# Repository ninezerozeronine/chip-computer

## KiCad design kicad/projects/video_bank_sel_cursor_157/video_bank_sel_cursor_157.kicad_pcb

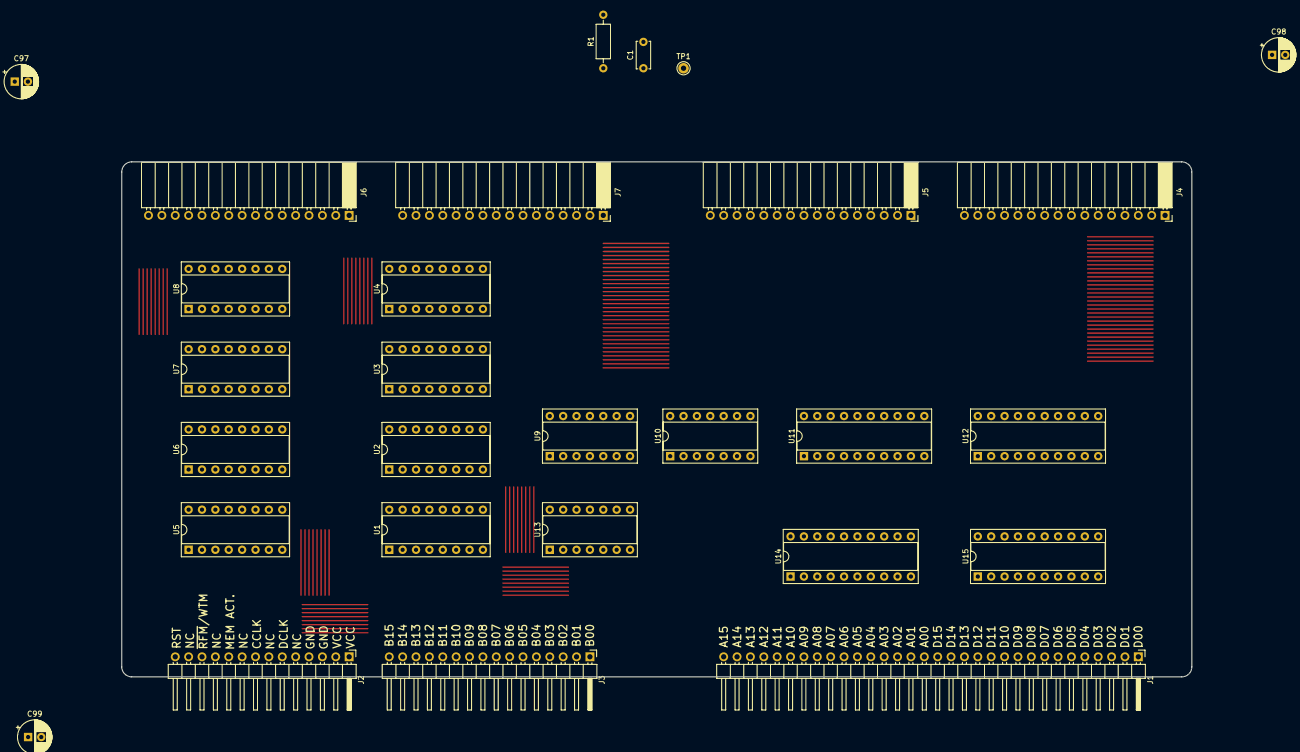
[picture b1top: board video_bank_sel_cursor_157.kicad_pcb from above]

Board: 2 copper layers, 203.2 x 97.8 mm, 28 parts (0 on the bottom side), 2 nets.

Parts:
C1: C; C_Disc_D5.0mm_W2.5mm_P5.00mm
C97, C98, C99: C_Polarized; CP_Radial_D6.3mm_P2.50mm
J1: peripheral_addr_bus_connector; peripheral-backplane-data-addr-anno
J2: peripheral_aux_connector; peripheral-backplane-aux
J3: peripheral_membank_connector; peripheral-backplane-membank
J4, J5, J6, J7: Conn_01x16_Socket; PinSocket_1x16_P2.54mm_Horizontal
R1: R_US; R_Axial_DIN0207_L6.3mm_D2.5mm_P10.16mm_Horizontal
TP1: TestPoint; Pin_D1.0mm_L10.0mm
U1, U2, U3, U4, U5, U6, U7, U8: 74HC157; DIP-16_W7.62mm_Socket
U9, U10: 74HC10; DIP-14_W7.62mm_Socket
U11, U12: 74HC377; DIP-20_W7.62mm_Socket
U13: 74HC04; DIP-14_W7.62mm_Socket
U14, U15: 74HC245; DIP-20_W7.62mm_Socket

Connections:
GND: C97.2, C98.2, C99.2, J2.3 (GND), J2.4 (GND)
VCC: C97.1, C98.1, C99.1, J2.1 (VCC), J2.2 (VCC)

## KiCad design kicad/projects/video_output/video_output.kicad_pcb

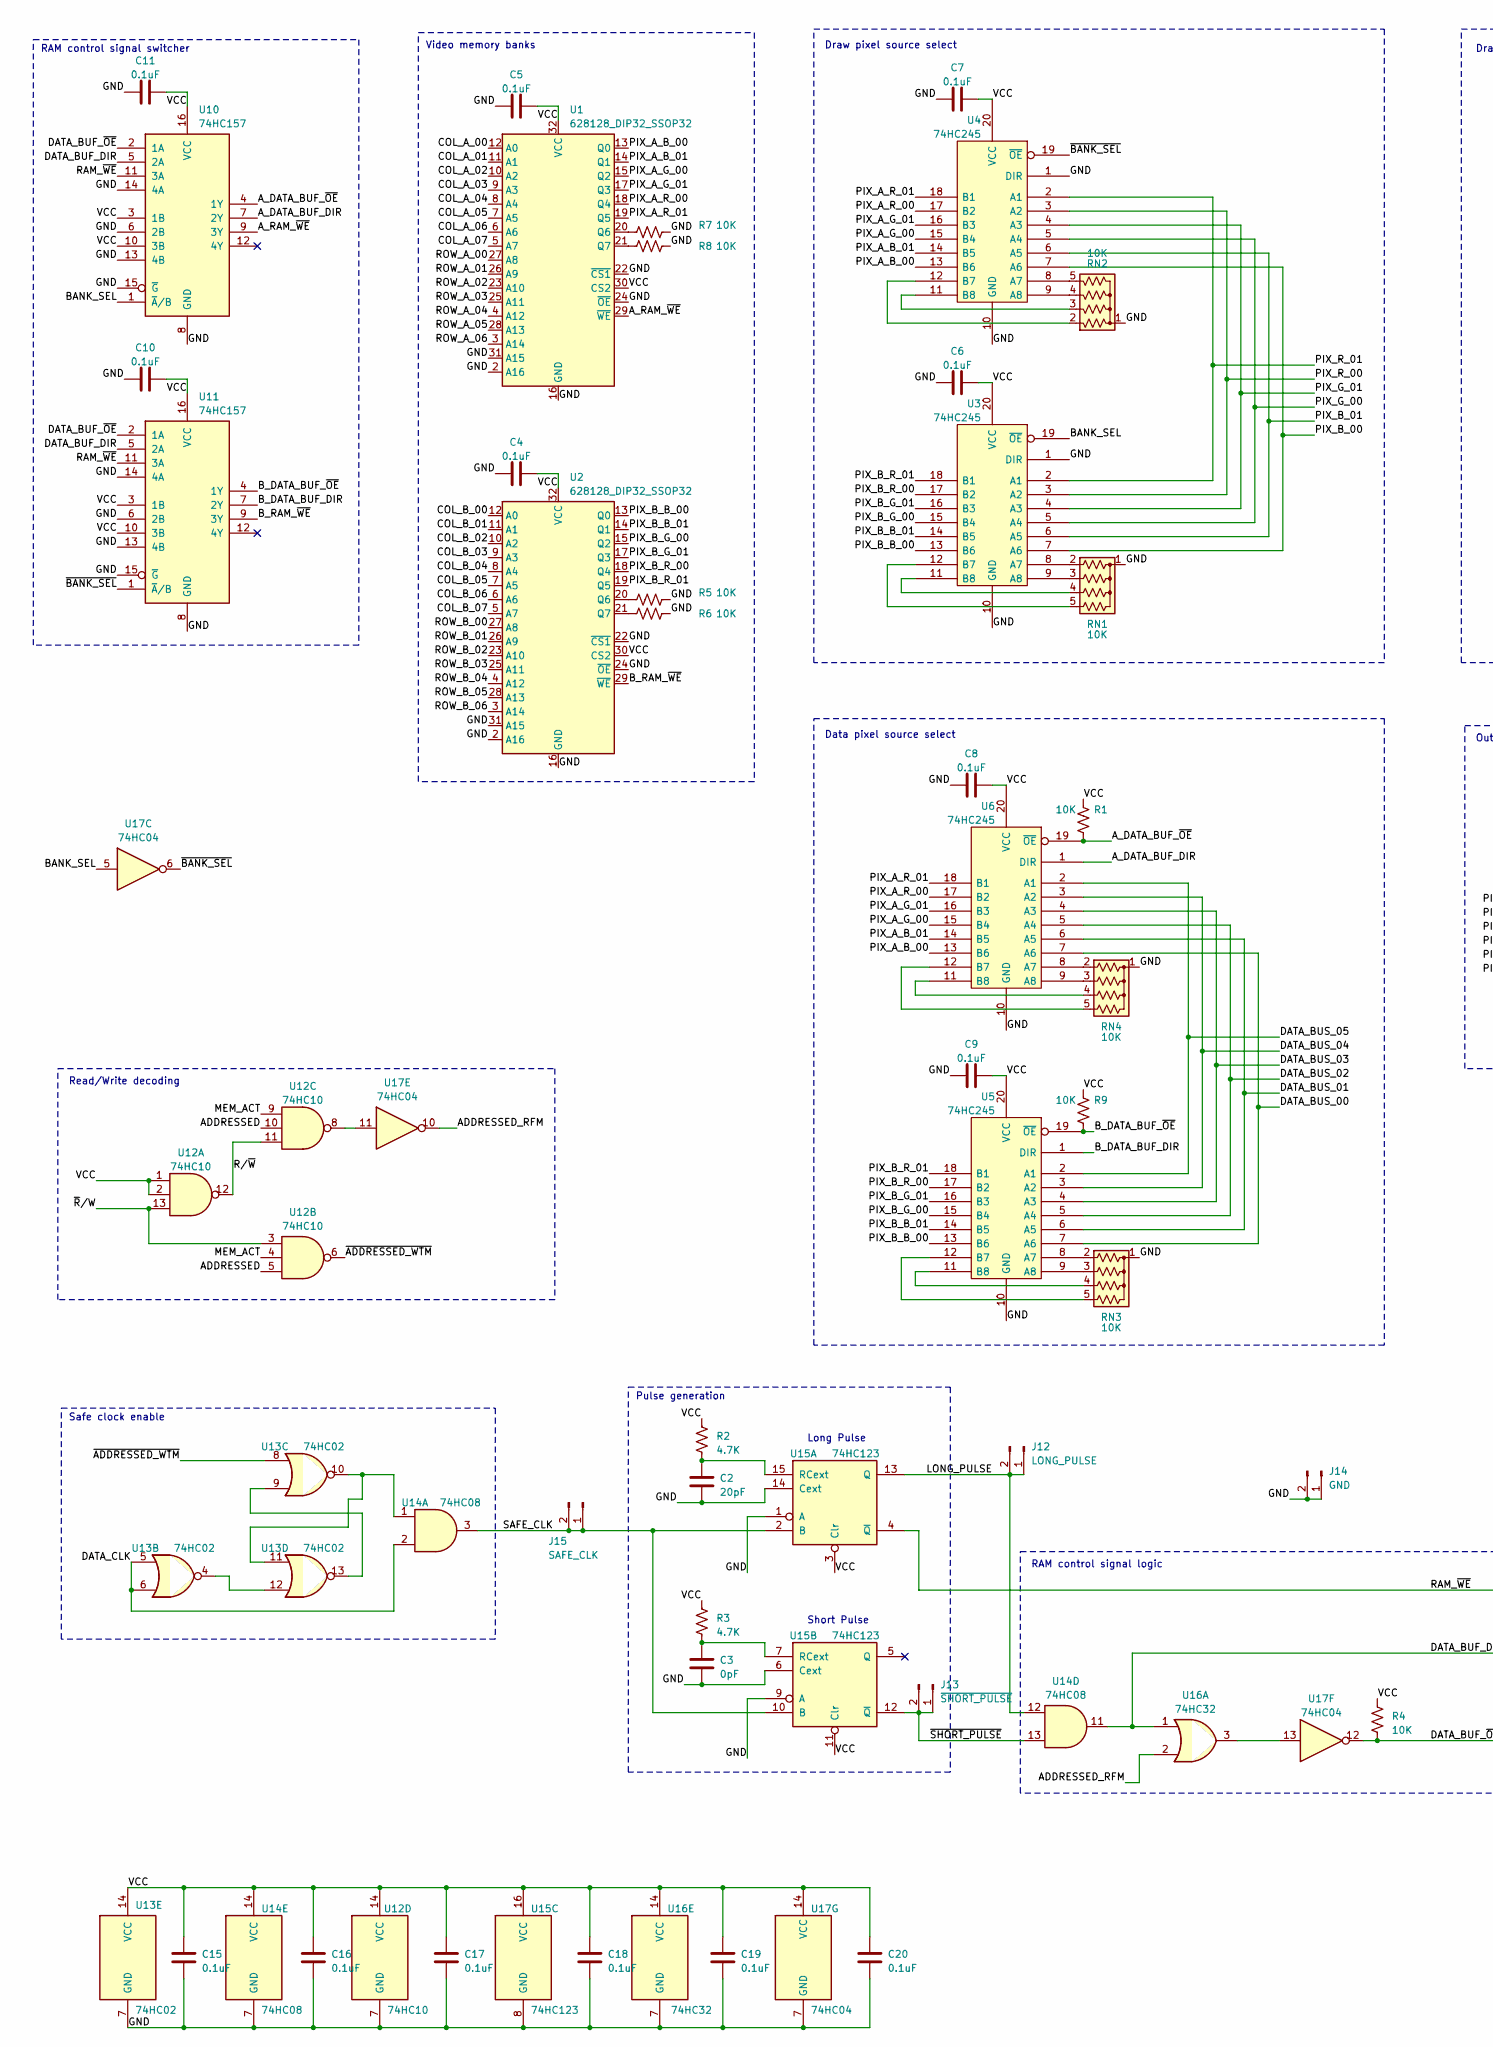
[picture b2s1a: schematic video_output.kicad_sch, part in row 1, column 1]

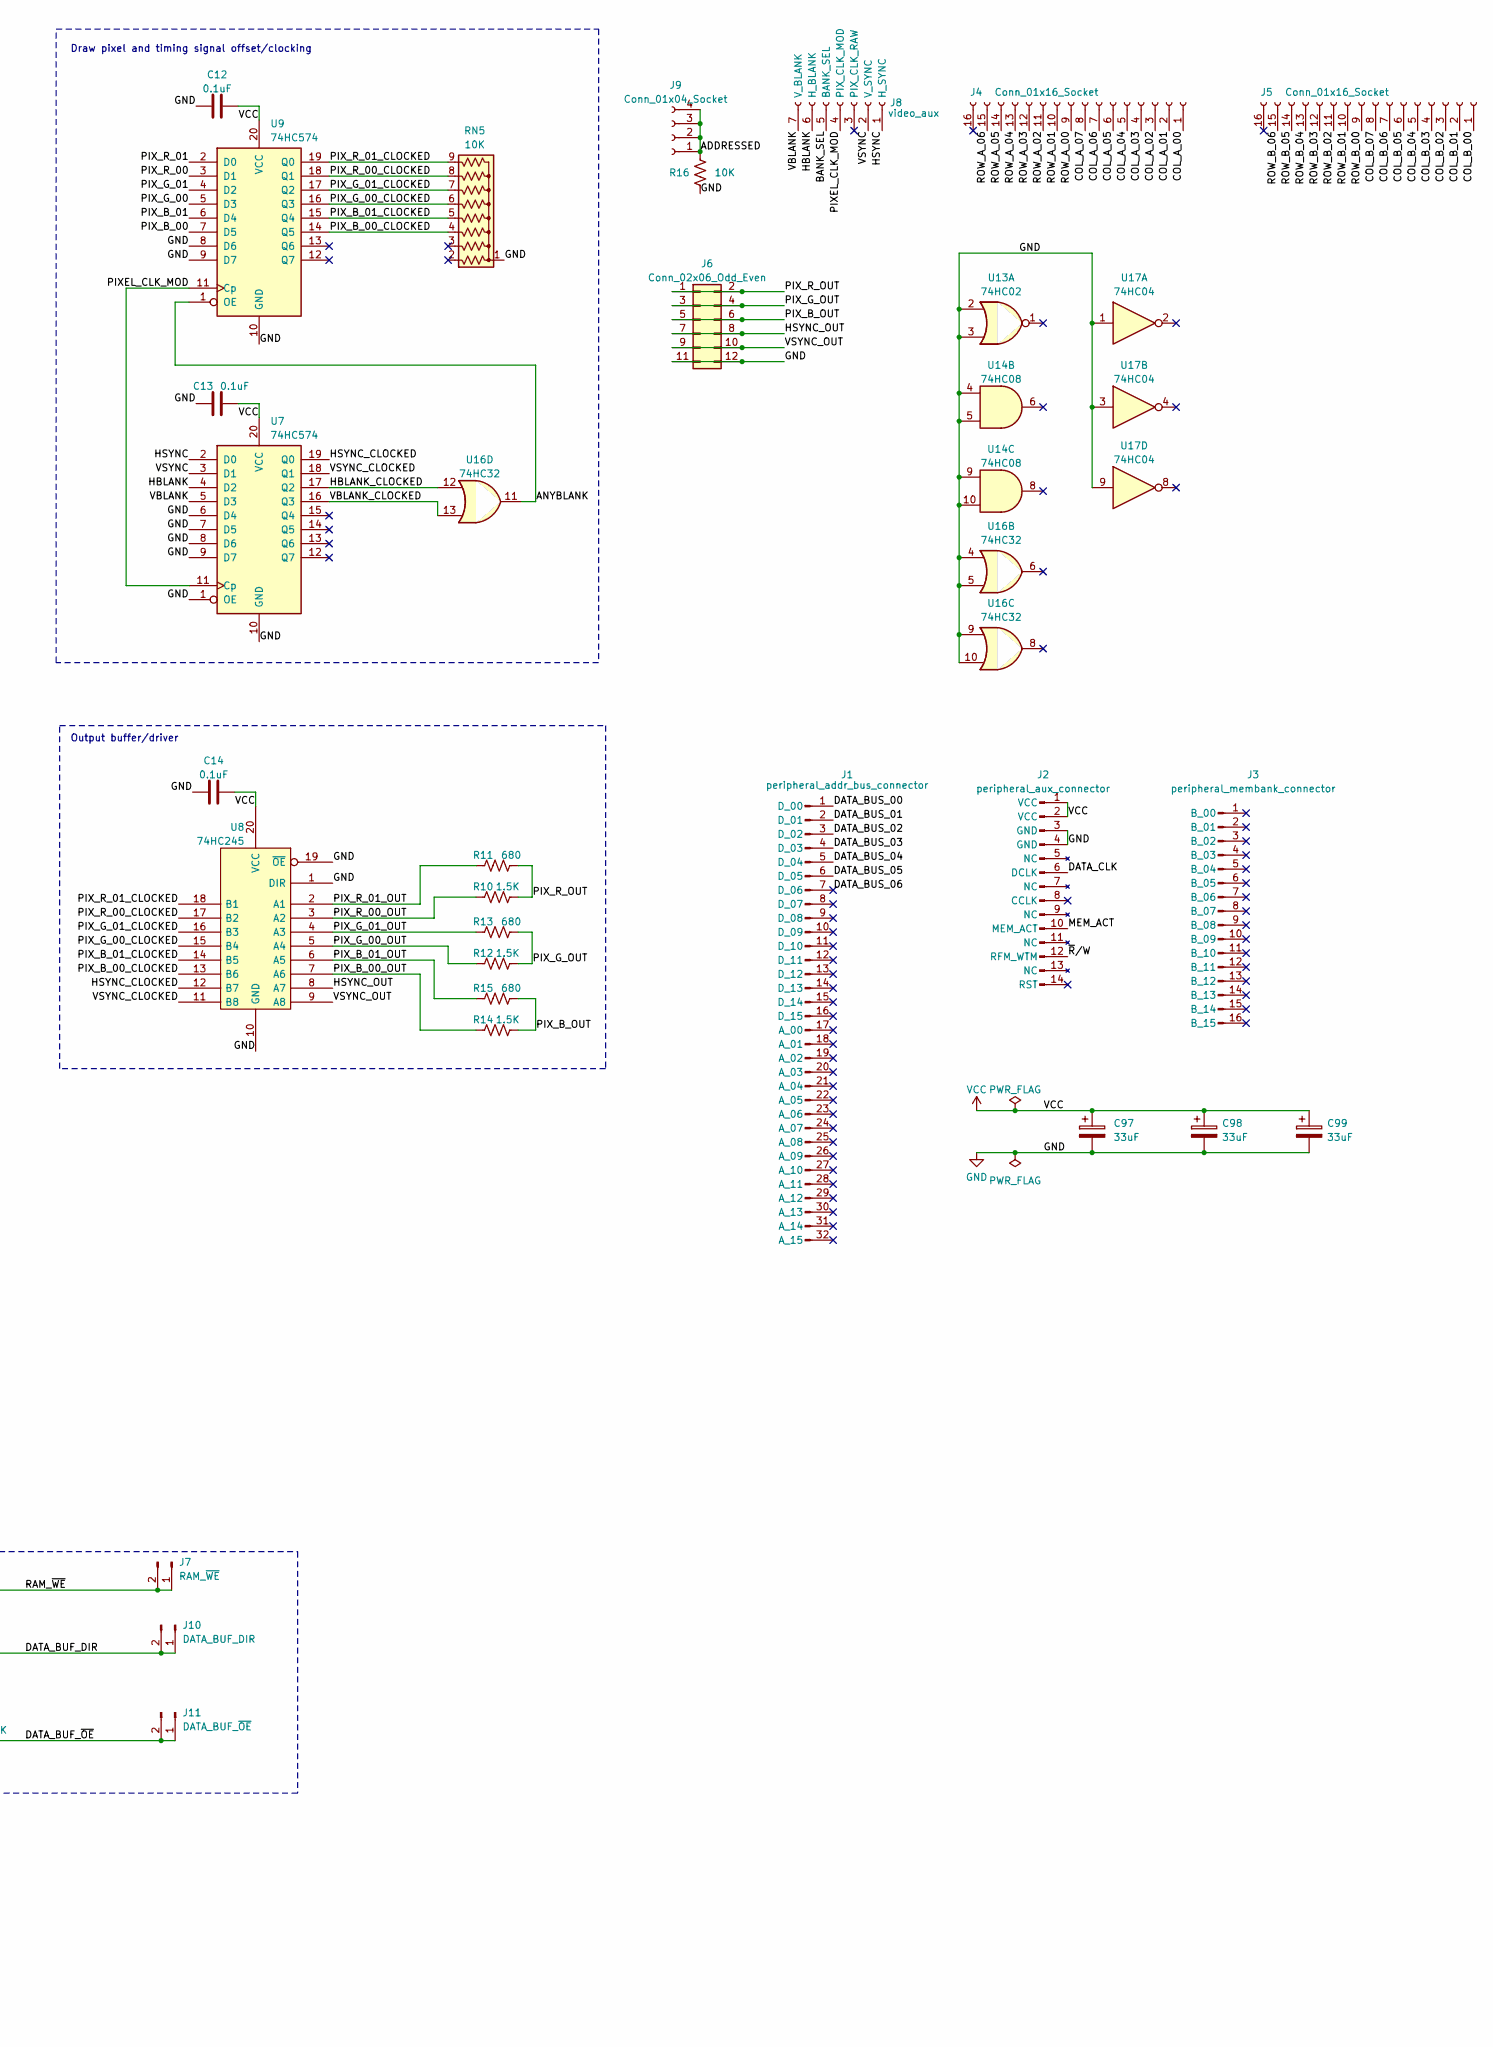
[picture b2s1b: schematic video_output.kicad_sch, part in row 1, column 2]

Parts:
C2: 20pF; C_Disc_D5.0mm_W2.5mm_P5.00mm
C3: 0pF; C_Disc_D5.0mm_W2.5mm_P5.00mm
C4, C5, C6, C7, C8, C9, C10, C11, C12, C13, C14, C15, C16, C17, C18, C19, C20: 0.1uF; C_Disc_D5.0mm_W2.5mm_P5.00mm
C97, C98, C99: 33uF; CP_Radial_D6.3mm_P2.50mm
J1: peripheral_addr_bus_connector; peripheral-backplane-data-addr-anno
J2: peripheral_aux_connector; peripheral-backplane-aux
J3: peripheral_membank_connector; peripheral-backplane-membank
J4, J5: Conn_01x16_Socket; PinSocket_1x16_P2.54mm_Horizontal
J6: Conn_02x06_Odd_Even; PinSocket_2x06_P2.54mm_Horizontal
J7: RAM_~{WE}; PinHeader_1x02_P2.54mm_Vertical
J8: video_aux; PinSocket_1x07_P2.54mm_Horizontal
J9: Conn_01x04_Socket; PinSocket_1x04_P2.54mm_Horizontal
J10: DATA_BUF_DIR; PinHeader_1x02_P2.54mm_Vertical
J11: DATA_BUF_~{OE}; PinHeader_1x02_P2.54mm_Vertical
J12: LONG_PULSE; PinHeader_1x02_P2.54mm_Vertical
J13: ~{SHORT_PULSE}; PinHeader_1x02_P2.54mm_Vertical
J14: GND; PinHeader_1x02_P2.54mm_Vertical
J15: SAFE_CLK; PinHeader_1x02_P2.54mm_Vertical
R1, R4, R5, R6, R7, R8, R9, R16: 10K; R_Axial_DIN0207_L6.3mm_D2.5mm_P10.16mm_Horizontal
R2, R3: 4.7K; R_Axial_DIN0207_L6.3mm_D2.5mm_P10.16mm_Horizontal
R10, R12, R14: 1.5K; R_Axial_DIN0207_L6.3mm_D2.5mm_P10.16mm_Horizontal
R11, R13, R15: 680; R_Axial_DIN0207_L6.3mm_D2.5mm_P10.16mm_Horizontal
RN1, RN2, RN3, RN4: 10K; R_Array_SIP5
RN5: 10K; R_Array_SIP9
U1, U2: 628128_DIP32_SSOP32; DIP-32_W15.24mm_Socket
U3, U4, U5, U6, U8: 74HC245; DIP-20_W7.62mm_Socket
U7, U9: 74HC574; DIP-20_W7.62mm_Socket
U10, U11: 74HC157; DIP-16_W7.62mm_Socket
U12: 74HC10; DIP-14_W7.62mm_Socket
U13: 74HC02; DIP-14_W7.62mm_Socket
U14: 74HC08; DIP-14_W7.62mm_Socket
U15: 74HC123; DIP-16_W7.62mm_Socket
U16: 74HC32; DIP-14_W7.62mm_Socket
U17: 74HC04; DIP-14_W7.62mm_Socket

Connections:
/ADDRESSED: J9.1, J9.2, J9.3, J9.4, R16.1, U12.5, U12.10
/ADDRESSED_RFM: U16.2, U17.10
/ANYBLANK: U9.1 (OE), U16.11
/A_DATA_BUF_DIR: U6.1 (DIR), U10.7 (2Y)
/A_DATA_BUF_~OE: R1.2, U6.19 (~OE), U10.4 (1Y)
/A_RAM_~WE: U1.29 (~WE), U10.9 (3Y)
/BANK_SEL: J8.5 (BANK_SEL), U3.19 (~OE), U10.1 (~A/B), U17.5
/B_DATA_BUF_DIR: U5.1 (DIR), U11.7 (2Y)
/B_DATA_BUF_~OE: R9.2, U5.19 (~OE), U11.4 (1Y)
/B_RAM_~WE: U2.29 (~WE), U11.9 (3Y)
/COL_A_00: J4.1, U1.12 (A0)
/COL_A_01: J4.2, U1.11 (A1)
/COL_A_02: J4.3, U1.10 (A2)
/COL_A_03: J4.4, U1.9 (A3)
/COL_A_04: J4.5, U1.8 (A4)
/COL_A_05: J4.6, U1.7 (A5)
/COL_A_06: J4.7, U1.6 (A6)
/COL_A_07: J4.8, U1.5 (A7)
/COL_B_00: J5.1, U2.12 (A0)
/COL_B_01: J5.2, U2.11 (A1)
/COL_B_02: J5.3, U2.10 (A2)
/COL_B_03: J5.4, U2.9 (A3)
/COL_B_04: J5.5, U2.8 (A4)
/COL_B_05: J5.6, U2.7 (A5)
/COL_B_06: J5.7, U2.6 (A6)
/COL_B_07: J5.8, U2.5 (A7)
/DATA_BUF_DIR: J10.1, J10.2, U10.5 (2A), U11.5 (2A), U14.11, U16.1
/DATA_BUF_~OE: J11.1, J11.2, R4.2, U10.2 (1A), U11.2 (1A), U17.12
/DATA_BUS_00: J1.1 (D_00), U5.7 (A6), U6.7 (A6)
/DATA_BUS_01: J1.2 (D_01), U5.6 (A5), U6.6 (A5)
/DATA_BUS_02: J1.3 (D_02), U5.5 (A4), U6.5 (A4)
/DATA_BUS_03: J1.4 (D_03), U5.4 (A3), U6.4 (A3)
/DATA_BUS_04: J1.5 (D_04), U5.3 (A2), U6.3 (A2)
/DATA_BUS_05: J1.6 (D_05), U5.2 (A1), U6.2 (A1)
/DATA_BUS_06: J1.7 (D_06)
/DATA_CLK: J2.6 (DCLK), U13.5, U13.6, U14.2
/HBLANK: J8.6 (H_BLANK), U7.4 (D2)
/HBLANK_CLOCKED: U7.17 (Q2), U16.12
/HSYNC: J8.1 (H_SYNC), U7.2 (D0)
/HSYNC_CLOCKED: U7.19 (Q0), U8.12 (B7)
/HSYNC_OUT: J6.7, J6.8, U8.8 (A7)
/LONG_PULSE: J12.1, J12.2, U14.12, U15.13 (Q)
/MEM_ACT: J2.10 (MEM_ACT), U12.4, U12.9
/PIXEL_CLK_MOD: J8.4 (PIX_CLK_MOD), U7.11 (Cp), U9.11 (Cp)
/PIX_A_B_00: U1.13 (Q0), U4.13 (B6), U6.13 (B6)
/PIX_A_B_01: U1.14 (Q1), U4.14 (B5), U6.14 (B5)
/PIX_A_G_00: U1.15 (Q2), U4.15 (B4), U6.15 (B4)
/PIX_A_G_01: U1.17 (Q3), U4.16 (B3), U6.16 (B3)
/PIX_A_R_00: U1.18 (Q4), U4.17 (B2), U6.17 (B2)
/PIX_A_R_01: U1.19 (Q5), U4.18 (B1), U6.18 (B1)
/PIX_B_00: U3.7 (A6), U4.7 (A6), U9.7 (D5)
/PIX_B_00_CLOCKED: RN5.4 (R3), U8.13 (B6), U9.14 (Q5)
/PIX_B_00_OUT: R14.1, U8.7 (A6)
/PIX_B_01: U3.6 (A5), U4.6 (A5), U9.6 (D4)
/PIX_B_01_CLOCKED: RN5.5 (R4), U8.14 (B5), U9.15 (Q4)
/PIX_B_01_OUT: R15.1, U8.6 (A5)
/PIX_B_B_00: U2.13 (Q0), U3.13 (B6), U5.13 (B6)
/PIX_B_B_01: U2.14 (Q1), U3.14 (B5), U5.14 (B5)
/PIX_B_G_00: U2.15 (Q2), U3.15 (B4), U5.15 (B4)
/PIX_B_G_01: U2.17 (Q3), U3.16 (B3), U5.16 (B3)
/PIX_B_OUT: J6.5, J6.6, R14.2, R15.2
/PIX_B_R_00: U2.18 (Q4), U3.17 (B2), U5.17 (B2)
/PIX_B_R_01: U2.19 (Q5), U3.18 (B1), U5.18 (B1)
/PIX_G_00: U3.5 (A4), U4.5 (A4), U9.5 (D3)
/PIX_G_00_CLOCKED: RN5.6 (R5), U8.15 (B4), U9.16 (Q3)
/PIX_G_00_OUT: R12.1, U8.5 (A4)
/PIX_G_01: U3.4 (A3), U4.4 (A3), U9.4 (D2)
/PIX_G_01_CLOCKED: RN5.7 (R6), U8.16 (B3), U9.17 (Q2)
/PIX_G_01_OUT: R13.1, U8.4 (A3)
/PIX_G_OUT: J6.3, J6.4, R12.2, R13.2
/PIX_R_00: U3.3 (A2), U4.3 (A2), U9.3 (D1)
/PIX_R_00_CLOCKED: RN5.8 (R7), U8.17 (B2), U9.18 (Q1)
/PIX_R_00_OUT: R10.1, U8.3 (A2)
/PIX_R_01: U3.2 (A1), U4.2 (A1), U9.2 (D0)
/PIX_R_01_CLOCKED: RN5.9 (R8), U8.18 (B1), U9.19 (Q0)
/PIX_R_01_OUT: R11.1, U8.2 (A1)
/PIX_R_OUT: J6.1, J6.2, R10.2, R11.2
/RAM_~WE: J7.1, J7.2, U10.11 (3A), U11.11 (3A), U15.4 (~Q)
/ROW_A_00: J4.9, U1.27 (A8)
/ROW_A_01: J4.10, U1.26 (A9)
/ROW_A_02: J4.11, U1.23 (A10)
/ROW_A_03: J4.12, U1.25 (A11)
/ROW_A_04: J4.13, U1.4 (A12)
/ROW_A_05: J4.14, U1.28 (A13)
/ROW_A_06: J4.15, U1.3 (A14)
/ROW_B_00: J5.9, U2.27 (A8)
/ROW_B_01: J5.10, U2.26 (A9)
/ROW_B_02: J5.11, U2.23 (A10)
/ROW_B_03: J5.12, U2.25 (A11)
/ROW_B_04: J5.13, U2.4 (A12)
/ROW_B_05: J5.14, U2.28 (A13)
/ROW_B_06: J5.15, U2.3 (A14)
/R/~W: U12.11, U12.12
/SAFE_CLK: J15.1, J15.2, U14.3, U15.2 (B), U15.10 (B)
/VBLANK: J8.7 (V_BLANK), U7.5 (D3)
/VBLANK_CLOCKED: U7.16 (Q3), U16.13
/VSYNC: J8.2 (V_SYNC), U7.3 (D1)
/VSYNC_CLOCKED: U7.18 (Q1), U8.11 (B8)
/VSYNC_OUT: J6.9, J6.10, U8.9 (A8)
/~ADDRESSED_WTM: U12.6, U13.8
/~BANK_SEL: U4.19 (~OE), U11.1 (~A/B), U17.6
/~R/W: J2.12 (RFM_WTM), U12.3, U12.13
/~SHORT_PULSE: J13.1, J13.2, U14.13, U15.12 (~Q)
GND: C2.2, C3.2, C4.1, C5.1, C6.1, C7.1, C8.1, C9.1, C10.1, C11.1, C12.1, C13.1, C14.1, C15.2, C16.2, C17.2, C18.2, C19.2, C20.2, C97.2, C98.2, C99.2, J2.3 (GND), J2.4 (GND), J6.11, J6.12, J14.1, J14.2, R5.2, R6.2, R7.2, R8.2, R16.2, RN1.1 (common), RN2.1 (common), RN3.1 (common), RN4.1 (common), RN5.1 (common), U1.2 (A16), U1.16 (GND), U1.22 (~CS1), U1.24 (~OE), U1.31 (A15), U2.2 (A16), U2.16 (GND), U2.22 (~CS1), U2.24 (~OE), U2.31 (A15), U3.1 (DIR), U3.10 (GND), U4.1 (DIR), U4.10 (GND), U5.10 (GND), U6.10 (GND), U7.1 (OE), U7.6 (D4), U7.7 (D5), U7.8 (D6), U7.9 (D7), U7.10 (GND), U8.1 (DIR), U8.10 (GND), U8.19 (~OE), U9.8 (D6), U9.9 (D7), U9.10 (GND), U10.6 (2B), U10.8 (GND), U10.13 (4B), U10.14 (4A), U10.15 (~G), U11.6 (2B), U11.8 (GND), U11.13 (4B), U11.14 (4A), U11.15 (~G), U12.7 (GND), U13.2, U13.3, U13.7 (GND), U14.4, U14.5, U14.7 (GND), U14.9, U14.10, U15.1 (A), U15.6 (Cext), U15.8 (GND), U15.9 (A), U15.14 (Cext), U16.4, U16.5, U16.7 (GND), U16.9, U16.10, U17.1, U17.3, U17.7 (GND), U17.9
unnamed: RN1.2 (R1), U3.8 (A7)
unnamed: RN1.3 (R2), U3.9 (A8)
unnamed: RN1.4 (R3), U3.11 (B8)
unnamed: RN1.5 (R4), U3.12 (B7)
unnamed: RN2.2 (R1), U4.12 (B7)
unnamed: RN2.3 (R2), U4.11 (B8)
unnamed: RN2.4 (R3), U4.9 (A8)
unnamed: RN2.5 (R4), U4.8 (A7)
unnamed: RN3.2 (R1), U5.8 (A7)
unnamed: RN3.3 (R2), U5.9 (A8)
unnamed: RN3.4 (R3), U5.11 (B8)
unnamed: RN3.5 (R4), U5.12 (B7)
unnamed: RN4.2 (R1), U6.8 (A7)
unnamed: RN4.3 (R2), U6.9 (A8)
unnamed: RN4.4 (R3), U6.11 (B8)
unnamed: RN4.5 (R4), U6.12 (B7)
unnamed: R7.1, U1.20 (Q6)
unnamed: R8.1, U1.21 (Q7)
unnamed: R5.1, U2.20 (Q6)
unnamed: R6.1, U2.21 (Q7)
unnamed: U12.8, U17.11
unnamed: U13.10, U13.11, U14.1
unnamed: U13.4, U13.12
unnamed: U13.9, U13.13
unnamed: C2.1, R2.2, U15.15 (RCext)
unnamed: C3.1, R3.2, U15.7 (RCext)
unnamed: U16.3, U17.13
VCC: C4.2, C5.2, C6.2, C7.2, C8.2, C9.2, C10.2, C11.2, C12.2, C13.2, C14.2, C15.1, C16.1, C17.1, C18.1, C19.1, C20.1, C97.1, C98.1, C99.1, J2.1 (VCC), J2.2 (VCC), R1.1, R2.1, R3.1, R4.1, R9.1, U1.30 (CS2), U1.32 (VCC), U2.30 (CS2), U2.32 (VCC), U3.20 (VCC), U4.20 (VCC), U5.20 (VCC), U6.20 (VCC), U7.20 (VCC), U8.20 (VCC), U9.20 (VCC), U10.3 (1B), U10.10 (3B), U10.16 (VCC), U11.3 (1B), U11.10 (3B), U11.16 (VCC), U12.1, U12.2, U12.14 (VCC), U13.14 (VCC), U14.14 (VCC), U15.3 (Clr), U15.11 (Clr), U15.16 (VCC), U16.14 (VCC), U17.14 (VCC)

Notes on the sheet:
Data pixel source select
Output buffer/driver
Long Pulse
Pulse generation
Video memory banks
Read/Write decoding
Draw pixel and timing signal offset/clocking
Draw pixel source select
RAM control signal logic
Safe clock enable
RAM control signal switcher
Short Pulse

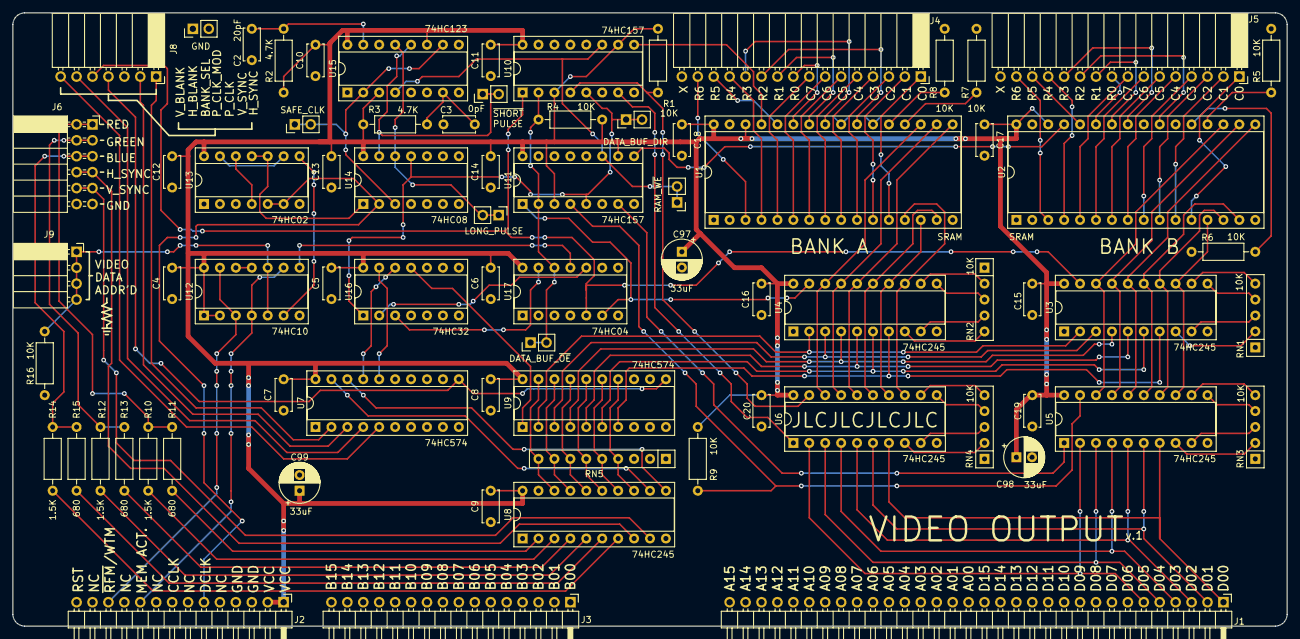
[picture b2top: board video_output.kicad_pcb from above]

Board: 2 copper layers, 203.2 x 97.8 mm, 75 parts (0 on the bottom side), 131 nets.

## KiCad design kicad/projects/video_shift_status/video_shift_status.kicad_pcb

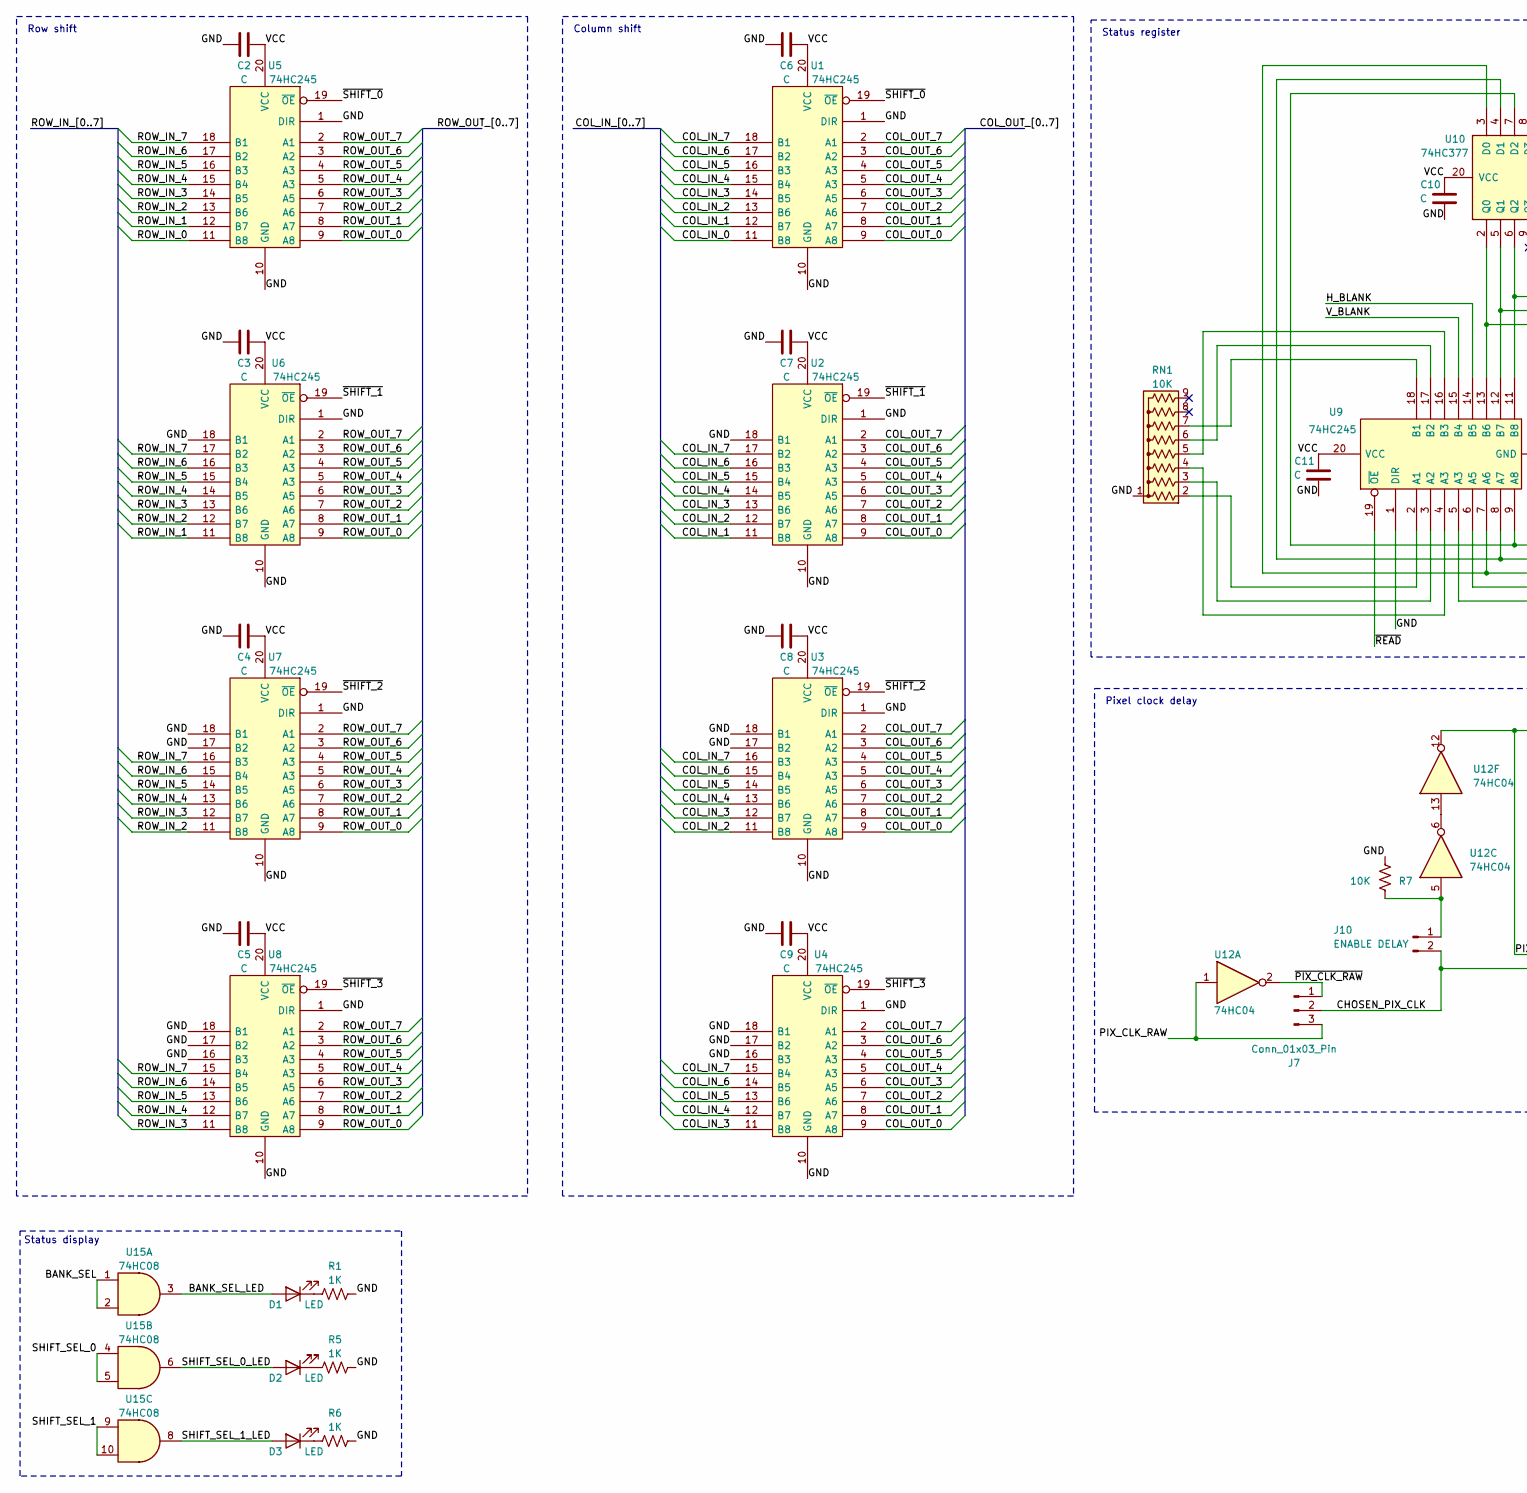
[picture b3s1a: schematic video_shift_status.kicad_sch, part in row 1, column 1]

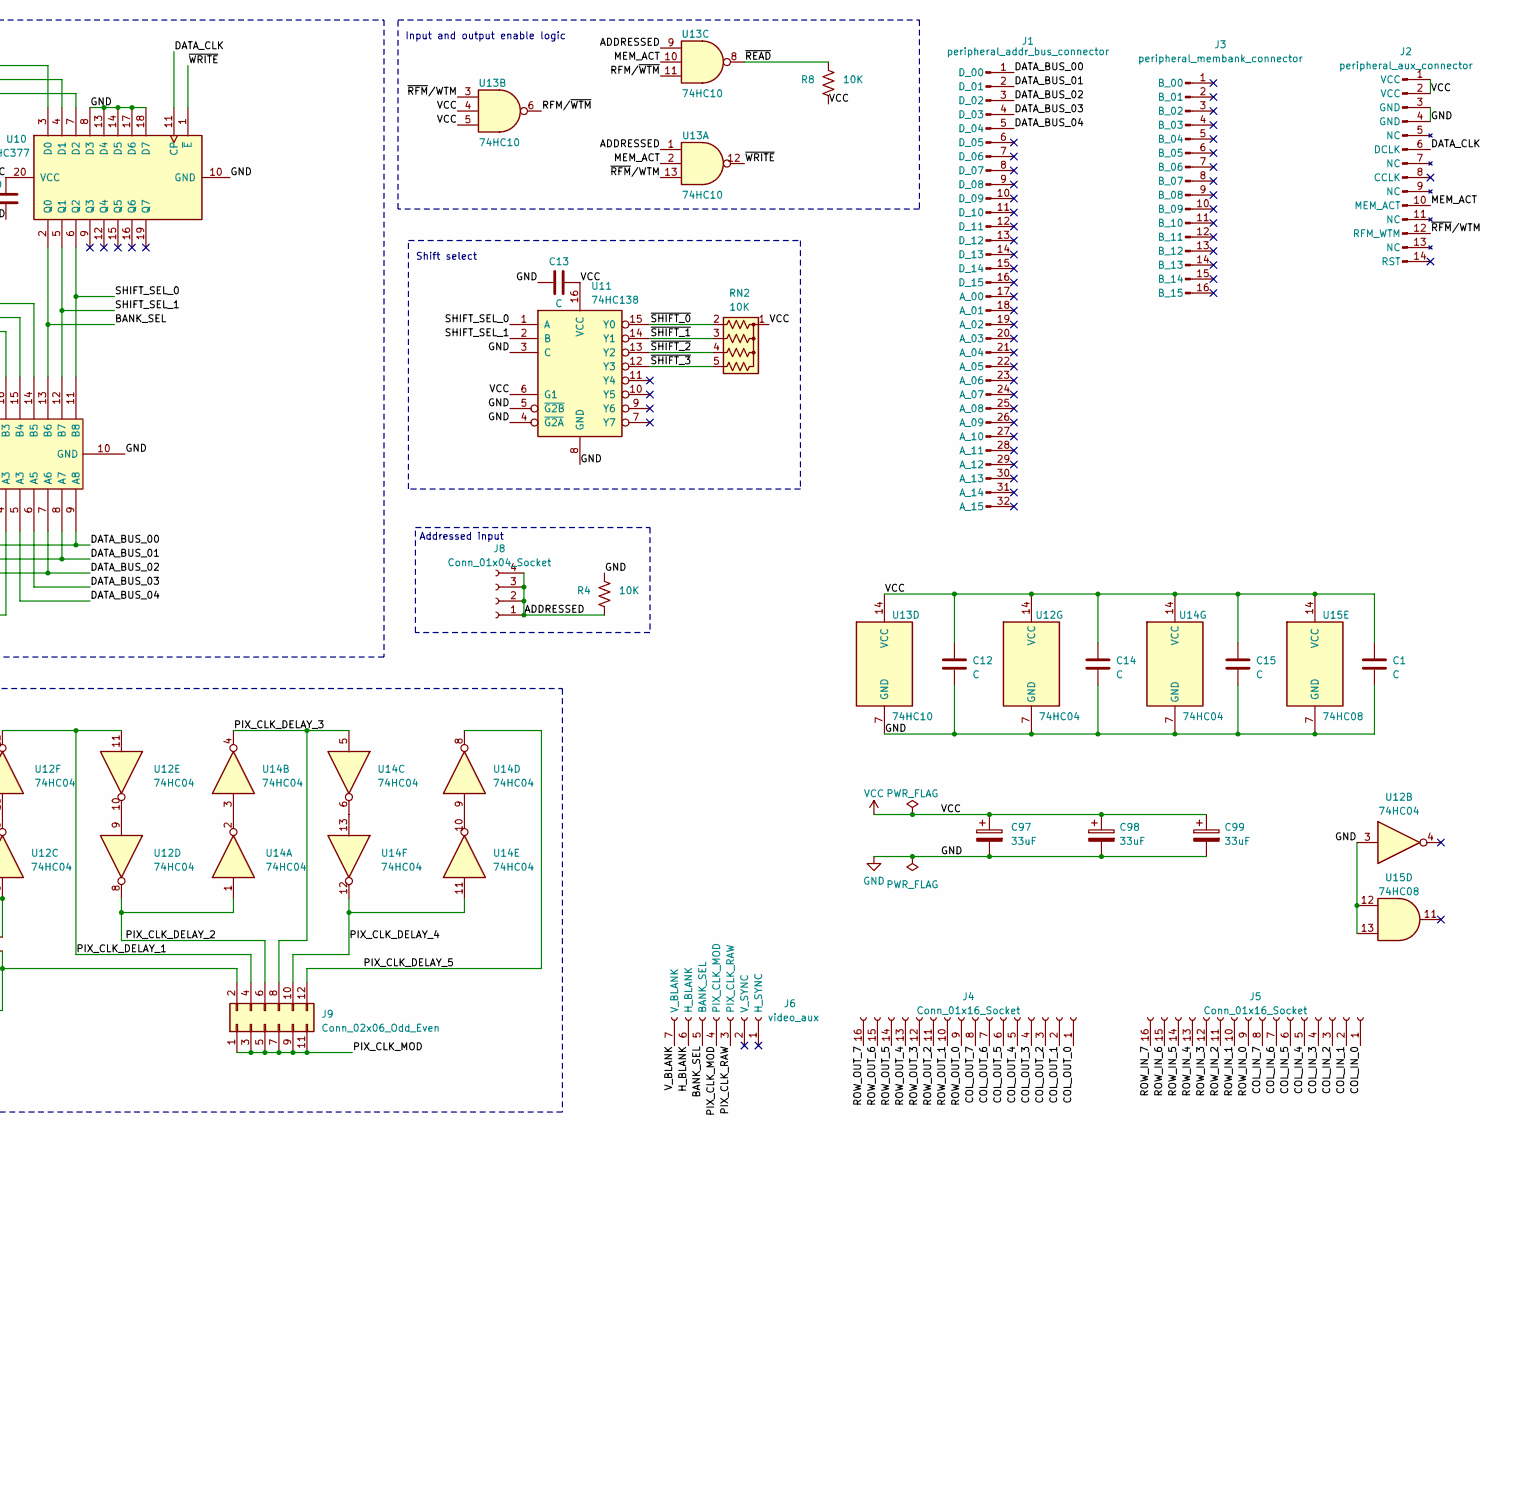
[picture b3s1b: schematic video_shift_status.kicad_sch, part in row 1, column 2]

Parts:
C1, C2, C3, C4, C5, C6, C7, C8, C9, C10, C11, C12, C13, C14, C15: C; C_Disc_D5.0mm_W2.5mm_P5.00mm
C97, C98, C99: 33uF; CP_Radial_D6.3mm_P2.50mm
D1, D2, D3: LED; LED_D5.0mm_Horizontal_O3.81mm_Z3.0mm
J1: peripheral_addr_bus_connector; peripheral-backplane-data-addr-anno
J2: peripheral_aux_connector; peripheral-backplane-aux
J3: peripheral_membank_connector; peripheral-backplane-membank
J4, J5: Conn_01x16_Socket; PinSocket_1x16_P2.54mm_Horizontal
J6: video_aux; PinSocket_1x07_P2.54mm_Horizontal
J7: Conn_01x03_Pin; PinHeader_1x03_P2.54mm_Vertical
J8: Conn_01x04_Socket; PinSocket_1x04_P2.54mm_Horizontal
J9: Conn_02x06_Odd_Even; PinHeader_2x06_P2.54mm_Vertical
J10: ENABLE DELAY; PinHeader_1x02_P2.54mm_Vertical
R1, R5, R6: 1K; R_Axial_DIN0207_L6.3mm_D2.5mm_P10.16mm_Horizontal
R4, R7, R8: 10K; R_Axial_DIN0207_L6.3mm_D2.5mm_P10.16mm_Horizontal
RN1: 10K; R_Array_SIP9
RN2: 10K; R_Array_SIP5
U1, U2, U3, U4, U5, U6, U7, U8, U9: 74HC245; DIP-20_W7.62mm_Socket
U10: 74HC377; DIP-20_W7.62mm_Socket
U11: 74HC138; DIP-16_W7.62mm_Socket
U12, U14: 74HC04; DIP-14_W7.62mm_Socket
U13: 74HC10; DIP-14_W7.62mm_Socket
U15: 74HC08; DIP-14_W7.62mm_Socket

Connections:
/ADDRESSED: J8.1, J8.2, J8.3, J8.4, R4.2, U13.1, U13.9
/BANK_SEL: J6.5 (BANK_SEL), U9.13 (B6), U10.2 (Q0), U15.1, U15.2
/BANK_SEL_LED: D1.2 (A), U15.3
/CHOSEN_PIX_CLK: J7.2, J9.2, J10.2
/COL_IN_0: J5.1, U1.11 (B8)
/COL_IN_1: J5.2, U1.12 (B7), U2.11 (B8)
/COL_IN_2: J5.3, U1.13 (B6), U2.12 (B7), U3.11 (B8)
/COL_IN_3: J5.4, U1.14 (B5), U2.13 (B6), U3.12 (B7), U4.11 (B8)
/COL_IN_4: J5.5, U1.15 (B4), U2.14 (B5), U3.13 (B6), U4.12 (B7)
/COL_IN_5: J5.6, U1.16 (B3), U2.15 (B4), U3.14 (B5), U4.13 (B6)
/COL_IN_6: J5.7, U1.17 (B2), U2.16 (B3), U3.15 (B4), U4.14 (B5)
/COL_IN_7: J5.8, U1.18 (B1), U2.17 (B2), U3.16 (B3), U4.15 (B4)
/COL_OUT_0: J4.1, U1.9 (A8), U2.9 (A8), U3.9 (A8), U4.9 (A8)
/COL_OUT_1: J4.2, U1.8 (A7), U2.8 (A7), U3.8 (A7), U4.8 (A7)
/COL_OUT_2: J4.3, U1.7 (A6), U2.7 (A6), U3.7 (A6), U4.7 (A6)
/COL_OUT_3: J4.4, U1.6 (A5), U2.6 (A5), U3.6 (A5), U4.6 (A5)
/COL_OUT_4: J4.5, U1.5 (A3), U2.5 (A3), U3.5 (A3), U4.5 (A3)
/COL_OUT_5: J4.6, U1.4 (A3), U2.4 (A3), U3.4 (A3), U4.4 (A3)
/COL_OUT_6: J4.7, U1.3 (A2), U2.3 (A2), U3.3 (A2), U4.3 (A2)
/COL_OUT_7: J4.8, U1.2 (A1), U2.2 (A1), U3.2 (A1), U4.2 (A1)
/DATA_BUS_00: J1.1 (D_00), U9.9 (A8), U10.7 (D2)
/DATA_BUS_01: J1.2 (D_01), U9.8 (A7), U10.4 (D1)
/DATA_BUS_02: J1.3 (D_02), U9.7 (A6), U10.3 (D0)
/DATA_BUS_03: J1.4 (D_03), U9.6 (A5)
/DATA_BUS_04: J1.5 (D_04), U9.5 (A3)
/DATA_CLK: J2.6 (DCLK), U10.11 (CP)
/H_BLANK: J6.6 (H_BLANK), U9.14 (B5)
/MEM_ACT: J2.10 (MEM_ACT), U13.2, U13.10
/PIX_CLK_DELAY_1: J9.4, U12.11, U12.12
/PIX_CLK_DELAY_2: J9.6, U12.8, U14.1
/PIX_CLK_DELAY_3: J9.8, U14.4, U14.5
/PIX_CLK_DELAY_4: J9.10, U14.11, U14.12
/PIX_CLK_DELAY_5: J9.12, U14.8
/PIX_CLK_MOD: J6.4 (PIX_CLK_MOD), J9.1, J9.3, J9.5, J9.7, J9.9, J9.11
/PIX_CLK_RAW: J6.3 (PIX_CLK_RAW), J7.3, U12.1
/RFM/~WTM: U13.6, U13.11
/ROW_IN_0: J5.9, U5.11 (B8)
/ROW_IN_1: J5.10, U5.12 (B7), U6.11 (B8)
/ROW_IN_2: J5.11, U5.13 (B6), U6.12 (B7), U7.11 (B8)
/ROW_IN_3: J5.12, U5.14 (B5), U6.13 (B6), U7.12 (B7), U8.11 (B8)
/ROW_IN_4: J5.13, U5.15 (B4), U6.14 (B5), U7.13 (B6), U8.12 (B7)
/ROW_IN_5: J5.14, U5.16 (B3), U6.15 (B4), U7.14 (B5), U8.13 (B6)
/ROW_IN_6: J5.15, U5.17 (B2), U6.16 (B3), U7.15 (B4), U8.14 (B5)
/ROW_IN_7: J5.16, U5.18 (B1), U6.17 (B2), U7.16 (B3), U8.15 (B4)
/ROW_OUT_0: J4.9, U5.9 (A8), U6.9 (A8), U7.9 (A8), U8.9 (A8)
/ROW_OUT_1: J4.10, U5.8 (A7), U6.8 (A7), U7.8 (A7), U8.8 (A7)
/ROW_OUT_2: J4.11, U5.7 (A6), U6.7 (A6), U7.7 (A6), U8.7 (A6)
/ROW_OUT_3: J4.12, U5.6 (A5), U6.6 (A5), U7.6 (A5), U8.6 (A5)
/ROW_OUT_4: J4.13, U5.5 (A3), U6.5 (A3), U7.5 (A3), U8.5 (A3)
/ROW_OUT_5: J4.14, U5.4 (A3), U6.4 (A3), U7.4 (A3), U8.4 (A3)
/ROW_OUT_6: J4.15, U5.3 (A2), U6.3 (A2), U7.3 (A2), U8.3 (A2)
/ROW_OUT_7: J4.16, U5.2 (A1), U6.2 (A1), U7.2 (A1), U8.2 (A1)
/SHIFT_SEL_0: U9.11 (B8), U10.6 (Q2), U11.1 (A), U15.4, U15.5
/SHIFT_SEL_0_LED: D2.2 (A), U15.6
/SHIFT_SEL_1: U9.12 (B7), U10.5 (Q1), U11.2 (B), U15.9, U15.10
/SHIFT_SEL_1_LED: D3.2 (A), U15.8
/V_BLANK: J6.7 (V_BLANK), U9.15 (B4)
/~PIX_CLK_RAW: J7.1, U12.2
/~READ: R8.1, U9.19 (~OE), U13.8
/~RFM/WTM: J2.12 (RFM_WTM), U13.3, U13.13
/~SHIFT_0: RN2.2 (R1), U1.19 (~OE), U5.19 (~OE), U11.15 (Y0)
/~SHIFT_1: RN2.3 (R2), U2.19 (~OE), U6.19 (~OE), U11.14 (Y1)
/~SHIFT_2: RN2.4 (R3), U3.19 (~OE), U7.19 (~OE), U11.13 (Y2)
/~SHIFT_3: RN2.5 (R4), U4.19 (~OE), U8.19 (~OE), U11.12 (Y3)
/~WRITE: U10.1 (~E), U13.12
GND: C1.2, C2.1, C3.1, C4.1, C5.1, C6.1, C7.1, C8.1, C9.1, C10.1, C11.1, C12.2, C13.1, C14.2, C15.2, C97.2, C98.2, C99.2, J2.3 (GND), J2.4 (GND), R1.2, R4.1, R5.2, R6.2, R7.2, RN1.1 (common), U1.1 (DIR), U1.10 (GND), U2.1 (DIR), U2.10 (GND), U2.18 (B1), U3.1 (DIR), U3.10 (GND), U3.17 (B2), U3.18 (B1), U4.1 (DIR), U4.10 (GND), U4.16 (B3), U4.17 (B2), U4.18 (B1), U5.1 (DIR), U5.10 (GND), U6.1 (DIR), U6.10 (GND), U6.18 (B1), U7.1 (DIR), U7.10 (GND), U7.17 (B2), U7.18 (B1), U8.1 (DIR), U8.10 (GND), U8.16 (B3), U8.17 (B2), U8.18 (B1), U9.1 (DIR), U9.10 (GND), U10.8 (D3), U10.10 (GND), U10.13 (D4), U10.14 (D5), U10.17 (D6), U10.18 (D7), U11.3 (C), U11.4 (~G2A), U11.5 (~G2B), U11.8 (GND), U12.3, U12.7 (GND), U13.7 (GND), U14.7 (GND), U15.7 (GND), U15.12, U15.13
unnamed: D1.1 (K), R1.1
unnamed: D2.1 (K), R5.1
unnamed: D3.1 (K), R6.1
unnamed: J10.1, R7.1, U12.5
unnamed: RN1.2 (R1), U9.2 (A1)
unnamed: RN1.3 (R2), U9.3 (A2)
unnamed: RN1.4 (R3), U9.4 (A3)
unnamed: RN1.5 (R4), U9.16 (B3)
unnamed: RN1.6 (R5), U9.17 (B2)
unnamed: RN1.7 (R6), U9.18 (B1)
unnamed: U12.9, U12.10
unnamed: U12.6, U12.13
unnamed: U14.2, U14.3
unnamed: U14.9, U14.10
unnamed: U14.6, U14.13
VCC: C1.1, C2.2, C3.2, C4.2, C5.2, C6.2, C7.2, C8.2, C9.2, C10.2, C11.2, C12.1, C13.2, C14.1, C15.1, C97.1, C98.1, C99.1, J2.1 (VCC), J2.2 (VCC), R8.2, RN2.1 (common), U1.20 (VCC), U2.20 (VCC), U3.20 (VCC), U4.20 (VCC), U5.20 (VCC), U6.20 (VCC), U7.20 (VCC), U8.20 (VCC), U9.20 (VCC), U10.20 (VCC), U11.6 (G1), U11.16 (VCC), U12.14 (VCC), U13.4, U13.5, U13.14 (VCC), U14.14 (VCC), U15.14 (VCC)

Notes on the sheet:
Column shift
Addressed input
Row shift
Pixel clock delay
Status display
Status register
Input and output enable logic
Shift select

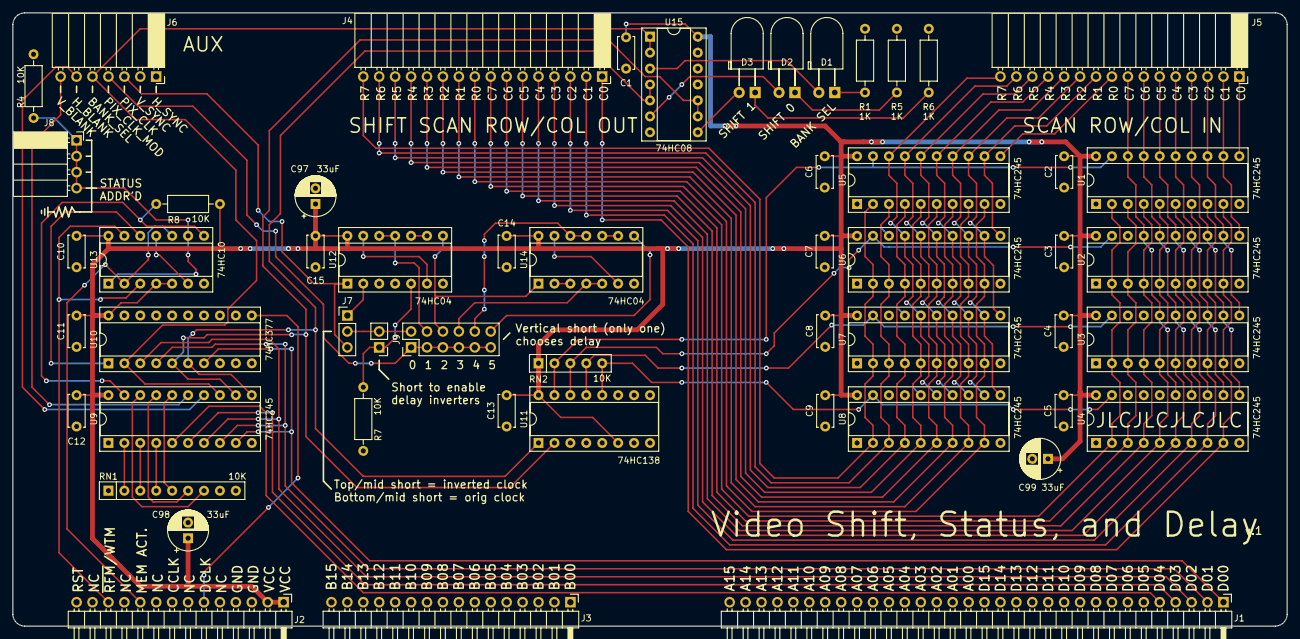
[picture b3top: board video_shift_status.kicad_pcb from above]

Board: 2 copper layers, 203.2 x 97.8 mm, 54 parts (0 on the bottom side), 82 nets.
